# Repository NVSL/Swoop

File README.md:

# Swoop -- Read and Write Autodesk Eagle Files in Python

Swoop is a library of Python objects for representing and manipulating
Autodesk Eagle board, schematic, and library files used in designing printed
circuit boards (PCBs).  It parses an input Eagle file, creates a internal
representation data structure that represents the file's contents,
provides accessors and mutators to query, read, and modify those contents, and
generates valid Eagle files as output.

Documentation is available here: http://nvsl.ucsd.edu/Swoop

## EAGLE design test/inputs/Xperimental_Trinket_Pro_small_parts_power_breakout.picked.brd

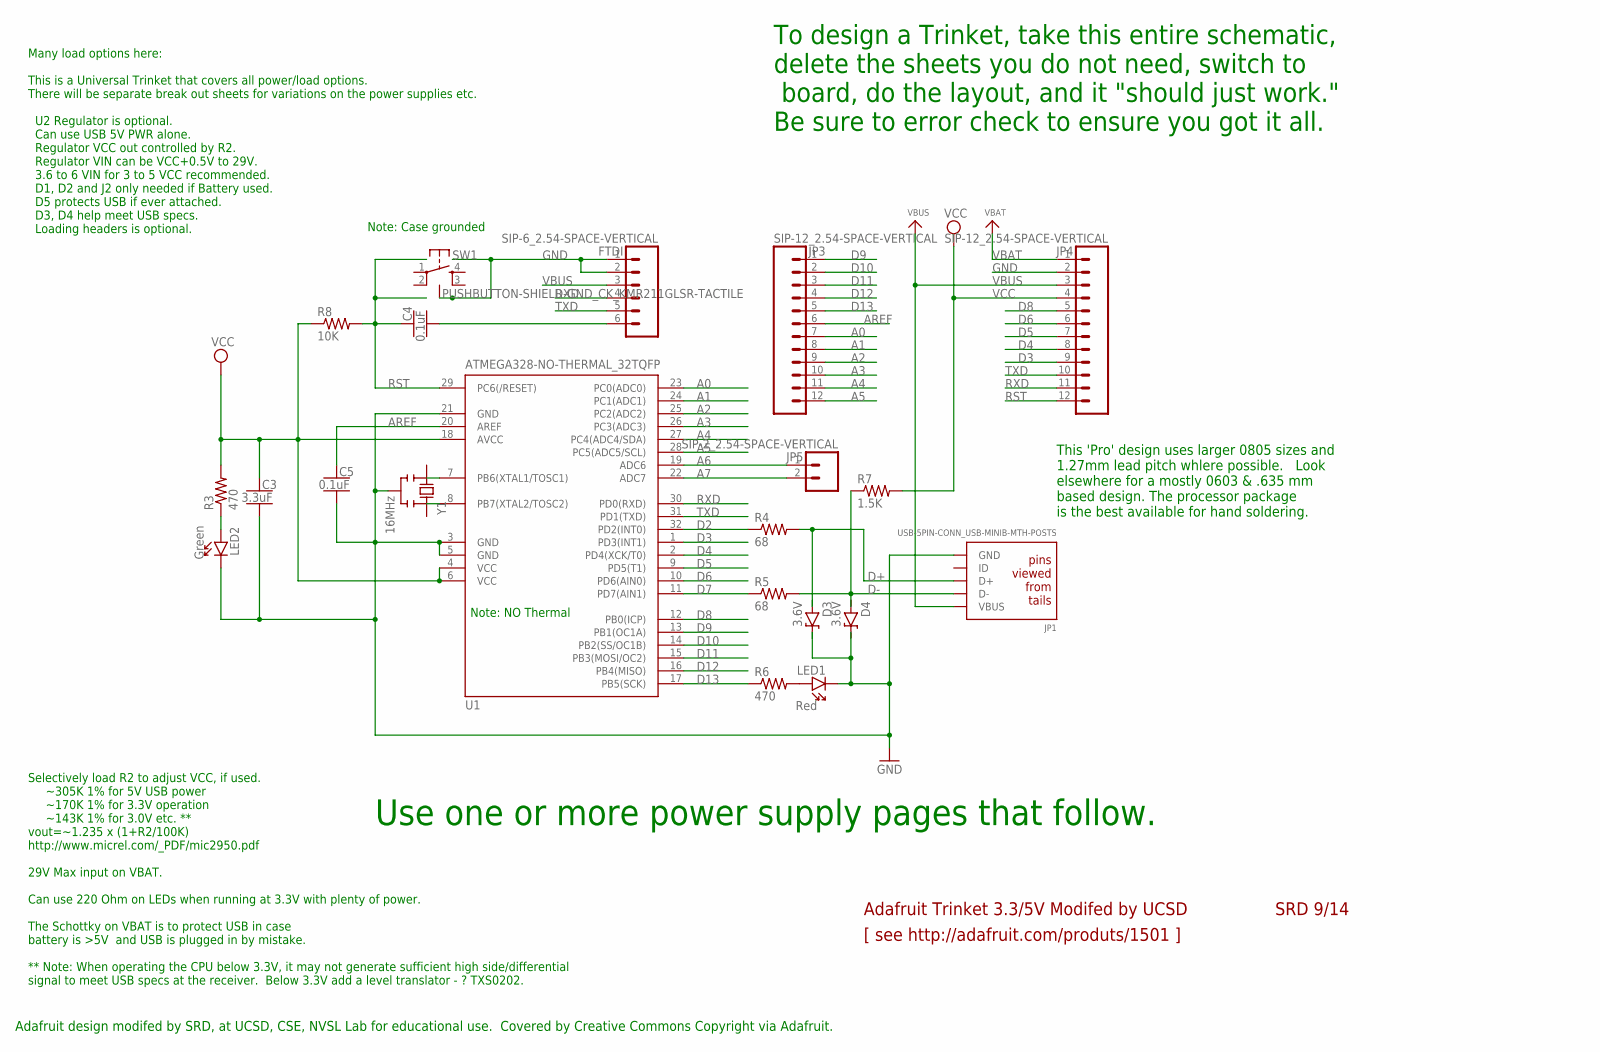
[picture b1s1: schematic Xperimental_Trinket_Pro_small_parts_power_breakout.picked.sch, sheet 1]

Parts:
C3: 3.3uF; CAPC2012X140_HS
C4, C5: 0.1uF; CAPRB500W53L600T350H600_HS
D3, D4: 3.6V; DIOAD1660W102L890D370_HS
FTDI: SIP-6_2.54-SPACE-VERTICAL; HDRV6W63P254_6X1_1524X254H838; MPN TSW-150-07-T-S
JP1: USB-5PIN-CONN_USB-MINIB-MTH-POSTS; FCI_10033526; MPN 10033526-N3212MLF
JP3, JP4: SIP-12_2.54-SPACE-VERTICAL; HDRV12W63P254_12X1_3048X254H838; MPN TSW-150-07-T-S
JP5: SIP-2_2.54-SPACE-VERTICAL; HDRV2W63P254_2X1_508X254H838; MPN TSW-150-07-T-S
LED1: Red; LEDRD250W50D400H640_HS
LED2: Green; LEDRD250W50D400H640_HS
R3, R6: 470; RESAD770W45L370D210_HS
R4, R5: 68; RESAD770W45L370D210_HS
R7: 1.5K; RESAD770W45L370D210_HS
R8: 10K; RESAD770W45L370D210_HS
SW1: PUSHBUTTON-SHIELD-GND_CK_KMR211GLSR-TACTILE; CK_KMR211GLSR; MPN KMR211GLFS
U1: ATMEGA328-NO-THERMAL_32TQFP; QFP80P900X900X120-32L30HS; MPN ATMEGA328-AU
Y1: 16MHz; MURATA_CTLS8_X_SERIES_HS

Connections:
A0: JP3.7, U1.23 (PC0(ADC0))
A1: JP3.8, U1.24 (PC1(ADC1))
A2: JP3.9, U1.25 (PC2(ADC2))
A3: JP3.10, U1.26 (PC3(ADC3))
A4: JP3.11, U1.27 (PC4(ADC4/SDA))
A5: JP3.12, U1.28 (PC5(ADC5/SCL))
A6: JP5.1, U1.19 (ADC6)
A7: JP5.2, U1.22 (ADC7)
AREF: C5.1, JP3.6, U1.20 (AREF)
D2: R4.1, U1.32 (PD2(INT0))
D3: JP4.9, U1.1 (PD3(INT1))
D4: JP4.8, U1.2 (PD4(XCK/T0))
D5: JP4.7, U1.9 (PD5(T1))
D6: JP4.6, U1.10 (PD6(AIN0))
D7: R5.1, U1.11 (PD7(AIN1))
D8: JP4.5, U1.12 (PB0(ICP))
D9: JP3.1, U1.13 (PB1(OC1A))
D10: JP3.2, U1.14 (PB2(SS/OC1B))
D11: JP3.3, U1.15 (PB3(MOSI/OC2))
D12: JP3.4, U1.16 (PB4(MISO))
D13: JP3.5, R6.1, U1.17 (PB5(SCK))
D+: D3.A, JP1.3 (D+), R4.2
D-: D4.A, JP1.2 (D-), R5.2, R7.1
DTR/RTS: C4.2, FTDI.6
GND: C3.2, C5.2, D3.C, D4.C, FTDI.1, FTDI.2, JP1.5 (GND), JP4.2, LED1.C, LED2.C, SW1.1, SW1.4, SW1.5, U1.3 (GND), U1.5 (GND), U1.21 (GND), Y1.2 (GND); also elsewhere on the board
unnamed: LED1.A, R6.2
unnamed: U1.8 (PB7(XTAL2/TOSC2)), Y1.1 (OSC2)
unnamed: U1.7 (PB6(XTAL1/TOSC1)), Y1.3 (OSC1)
unnamed: LED2.A, R3.1
RST: C4.1, JP4.12, R8.2, SW1.2, SW1.3, U1.29 (PC6(/RESET))
RXD: FTDI.4, JP4.11, U1.30 (PD0(RXD))
TXD: FTDI.5, JP4.10, U1.31 (PD1(TXD))
VBAT: JP4.1; also elsewhere on the board
VBUS: FTDI.3, JP1.1 (VBUS), JP4.3; also elsewhere on the board
VCC: C3.1, JP4.4, R3.2, R7.2, R8.1, U1.4 (VCC), U1.6 (VCC), U1.18 (AVCC); also elsewhere on the board

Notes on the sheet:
To design a Trinket, take this entire schematic, delete the sheets you do not need, switch to board, do the layout, and it "should just work." Be sure to error check to ensure you got it all.
[ see http://adafruit.com/produts/1501 ]
Adafruit Trinket 3.3/5V Modifed by UCSD
This 'Pro' design uses larger 0805 sizes and 1.27mm lead pitch whlere possible. Look elsewhere for a mostly 0603 & .635 mm based design. The processor package is the best available for hand soldering.
SRD 9/14
Adafruit design modifed by SRD, at UCSD, CSE, NVSL Lab for educational use. Covered by Creative Commons Copyright via Adafruit.
Many load options here: This is a Universal Trinket that covers all power/load options. There will be separate break out sheets for variations on the power supplies etc. U2 Regulator is optional. Can use USB 5V PWR alone. Regulator VCC out controlled by R2. Regulator VIN can be VCC+0.5V to 29V. 3.6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
Selectively load R2 to adjust VCC, if used. ~305K 1% for 5V USB power ~170K 1% for 3.3V operation ~143K 1% for 3.0V etc. ** vout=~1.235 x (1+R2/100K) http://www.micrel.com/_PDF/mic2950.pdf 29V Max input on VBAT. Can use 220 Ohm on LEDs when running at 3.3V with plenty of power. The Schottky on VBAT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
Note: Case grounded
Use one or more power supply pages that follow.
Note: NO Thermal

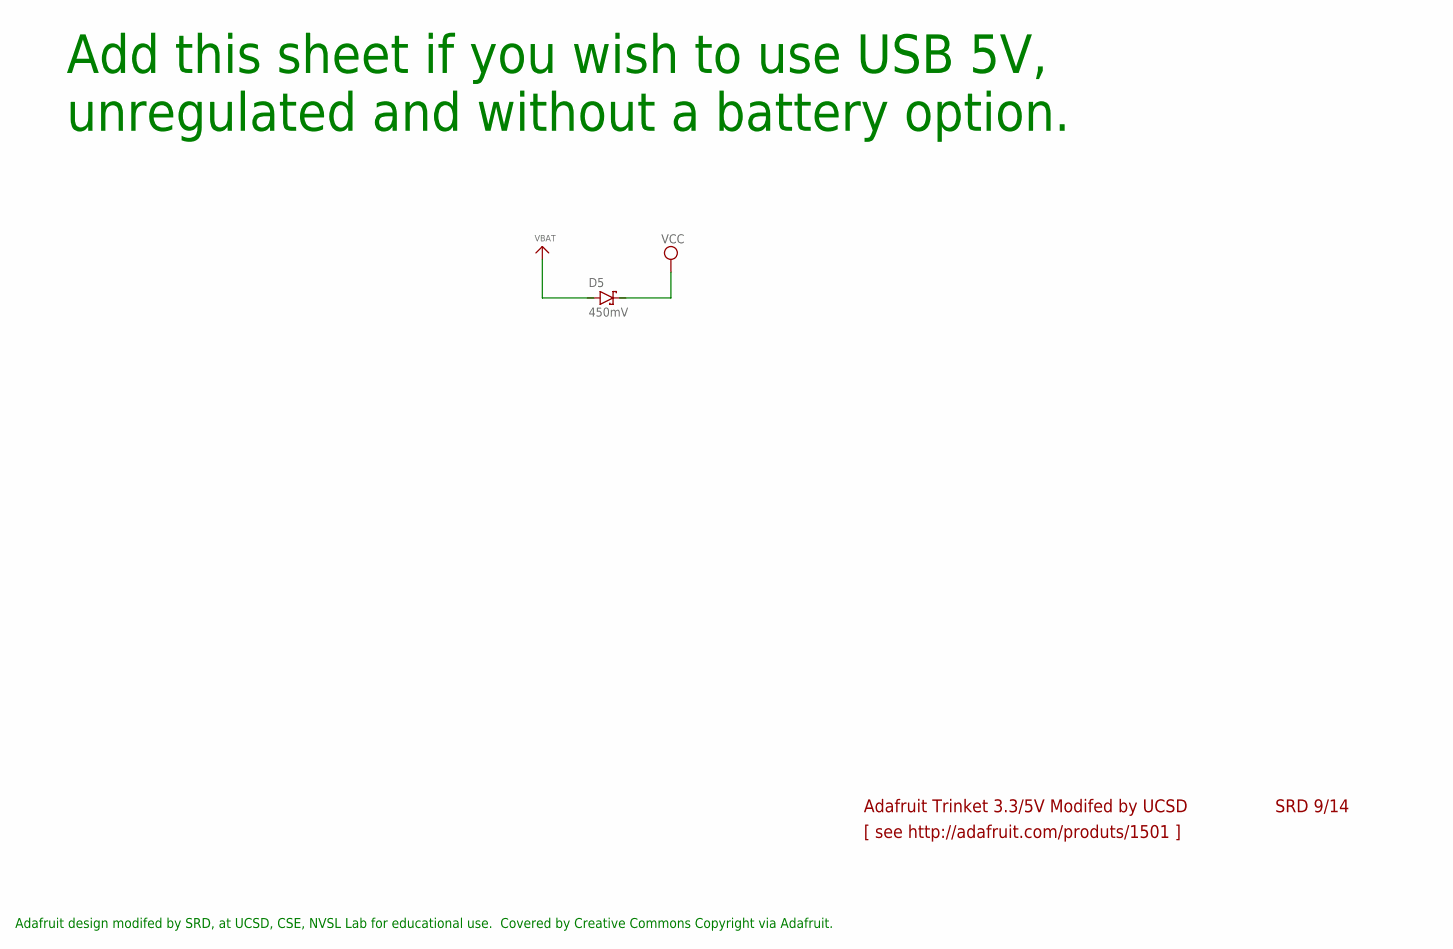
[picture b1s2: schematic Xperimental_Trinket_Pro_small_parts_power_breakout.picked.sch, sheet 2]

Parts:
D5: 450mV; DIOAD1125W78L520D270_HS

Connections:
VBAT: D5.A; also elsewhere on the board
VCC: D5.C; also elsewhere on the board

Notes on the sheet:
Add this sheet if you wish to use USB 5V, unregulated and without a battery option.
Adafruit design modifed by SRD, at UCSD, CSE, NVSL Lab for educational use. Covered by Creative Commons Copyright via Adafruit.
[ see http://adafruit.com/produts/1501 ]
Adafruit Trinket 3.3/5V Modifed by UCSD
SRD 9/14

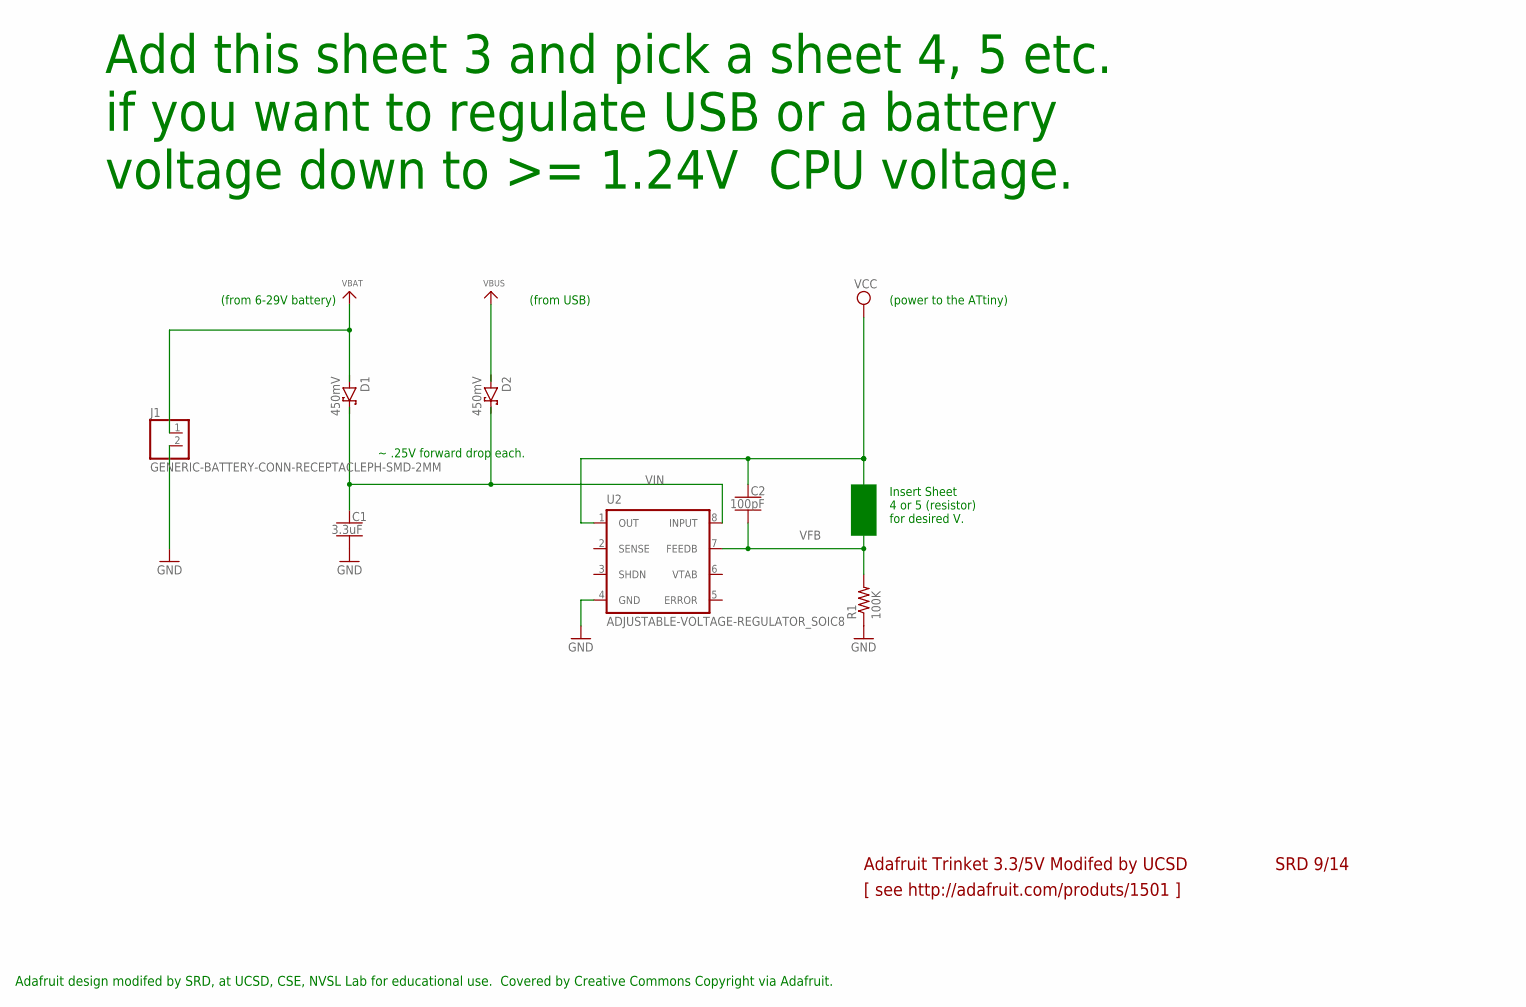
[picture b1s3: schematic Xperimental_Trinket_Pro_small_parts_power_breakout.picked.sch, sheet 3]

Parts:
C1: 3.3uF; CAPC2012X140_HS
C2: 100pF; CAPRB500W53L550T250H550_HS
D1, D2: 450mV; DIOAD1125W78L520D270_HS
J1: GENERIC-BATTERY-CONN-RECEPTACLEPH-SMD-2MM; JST_S2B-PH-SM4-TB; MPN S2B-PH-SM4-TB(LF)(SN)
R1: 100K; RESAD1160W55L680D260_HS
U2: ADJUSTABLE-VOLTAGE-REGULATOR_SOIC8; SOIC127P600X175-8L86HS; MPN MIC2951-03YM

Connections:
GND: C1.2, J1.2, R1.1, U2.4 (GND); also elsewhere on the board
VBAT: D1.A, J1.1; also elsewhere on the board
VBUS: D2.A; also elsewhere on the board
VCC: C2.1, U2.1 (OUT); also elsewhere on the board
VFB: C2.2, R1.2, U2.7 (FEEDB); also elsewhere on the board
VIN: C1.1, D1.C, D2.C, U2.8 (INPUT); also elsewhere on the board

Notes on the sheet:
(from USB)
[ see http://adafruit.com/produts/1501 ]
Adafruit Trinket 3.3/5V Modifed by UCSD
Insert Sheet 4 or 5 (resistor) for desired V.
(power to the ATtiny)
Add this sheet 3 and pick a sheet 4, 5 etc. if you want to regulate USB or a battery voltage down to >= 1.24V CPU voltage.
SRD 9/14
(from 6-29V battery)
Adafruit design modifed by SRD, at UCSD, CSE, NVSL Lab for educational use. Covered by Creative Commons Copyright via Adafruit.
~ .25V forward drop each.

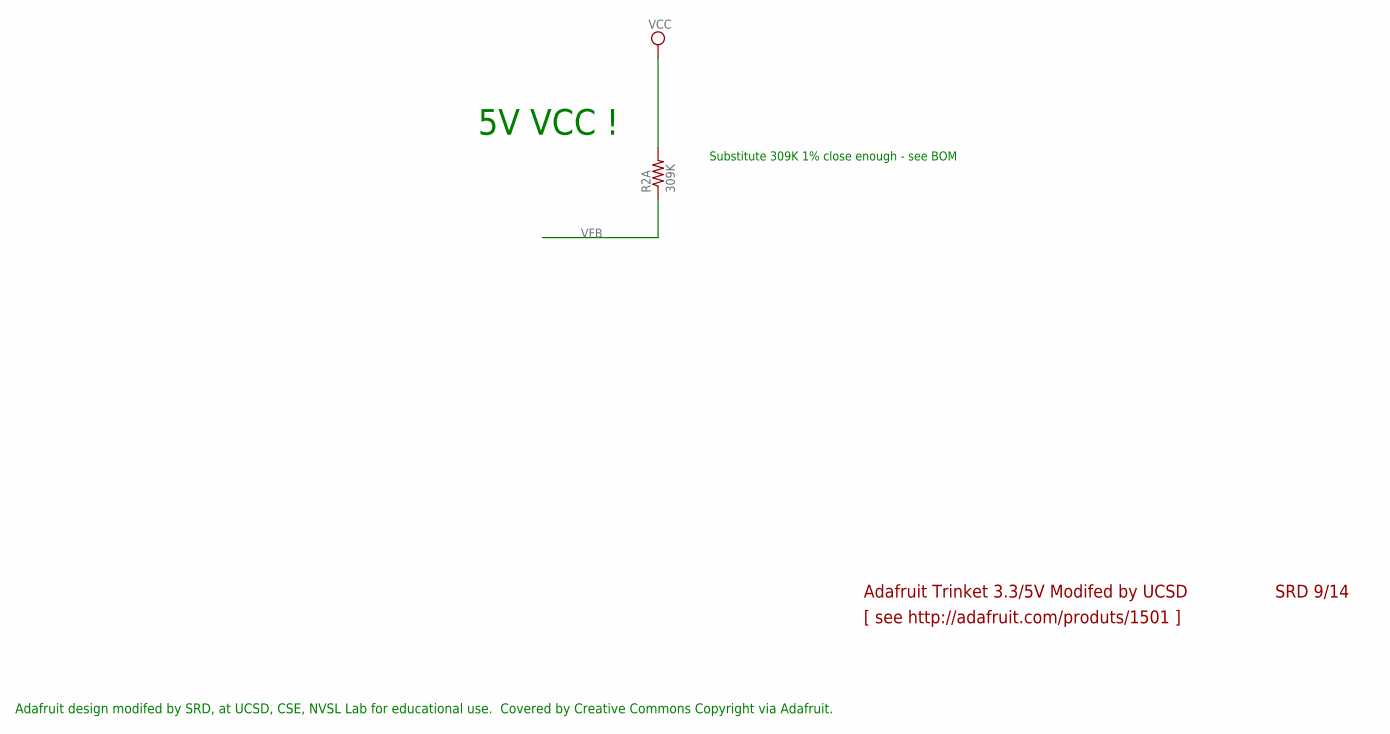
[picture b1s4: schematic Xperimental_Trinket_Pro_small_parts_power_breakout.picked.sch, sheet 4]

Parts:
R2A: 309K; RESAD1160W55L680D260_HS

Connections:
VCC: R2A.2; also elsewhere on the board
VFB: R2A.1; also elsewhere on the board

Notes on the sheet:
Substitute 309K 1% close enough - see BOM
[ see http://adafruit.com/produts/1501 ]
Adafruit Trinket 3.3/5V Modifed by UCSD
SRD 9/14
Adafruit design modifed by SRD, at UCSD, CSE, NVSL Lab for educational use. Covered by Creative Commons Copyright via Adafruit.
5V VCC !

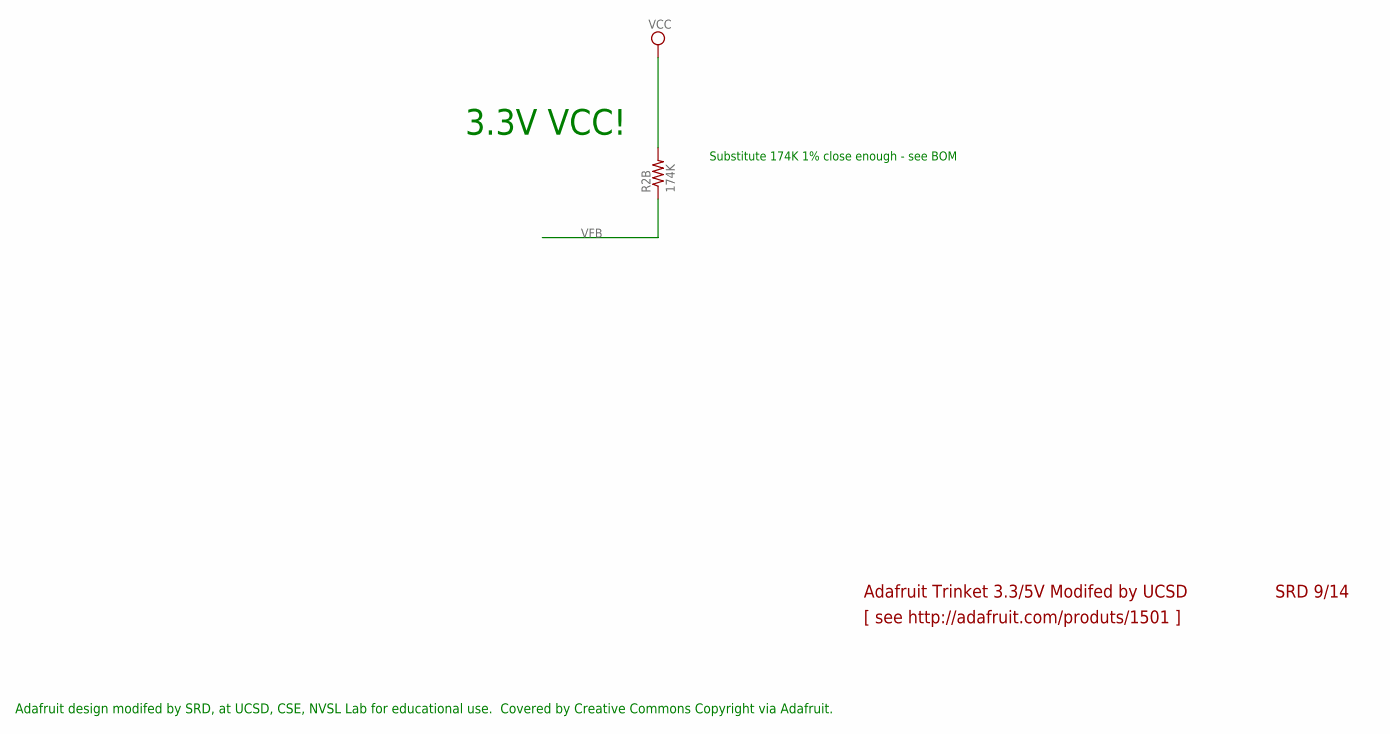
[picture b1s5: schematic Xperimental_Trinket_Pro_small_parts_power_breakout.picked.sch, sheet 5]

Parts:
R2B: 174K; RESAD1160W55L680D260_HS

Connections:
VCC: R2B.2; also elsewhere on the board
VFB: R2B.1; also elsewhere on the board

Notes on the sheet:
Substitute 174K 1% close enough - see BOM
[ see http://adafruit.com/produts/1501 ]
Adafruit Trinket 3.3/5V Modifed by UCSD
SRD 9/14
Adafruit design modifed by SRD, at UCSD, CSE, NVSL Lab for educational use. Covered by Creative Commons Copyright via Adafruit.
3.3V VCC!

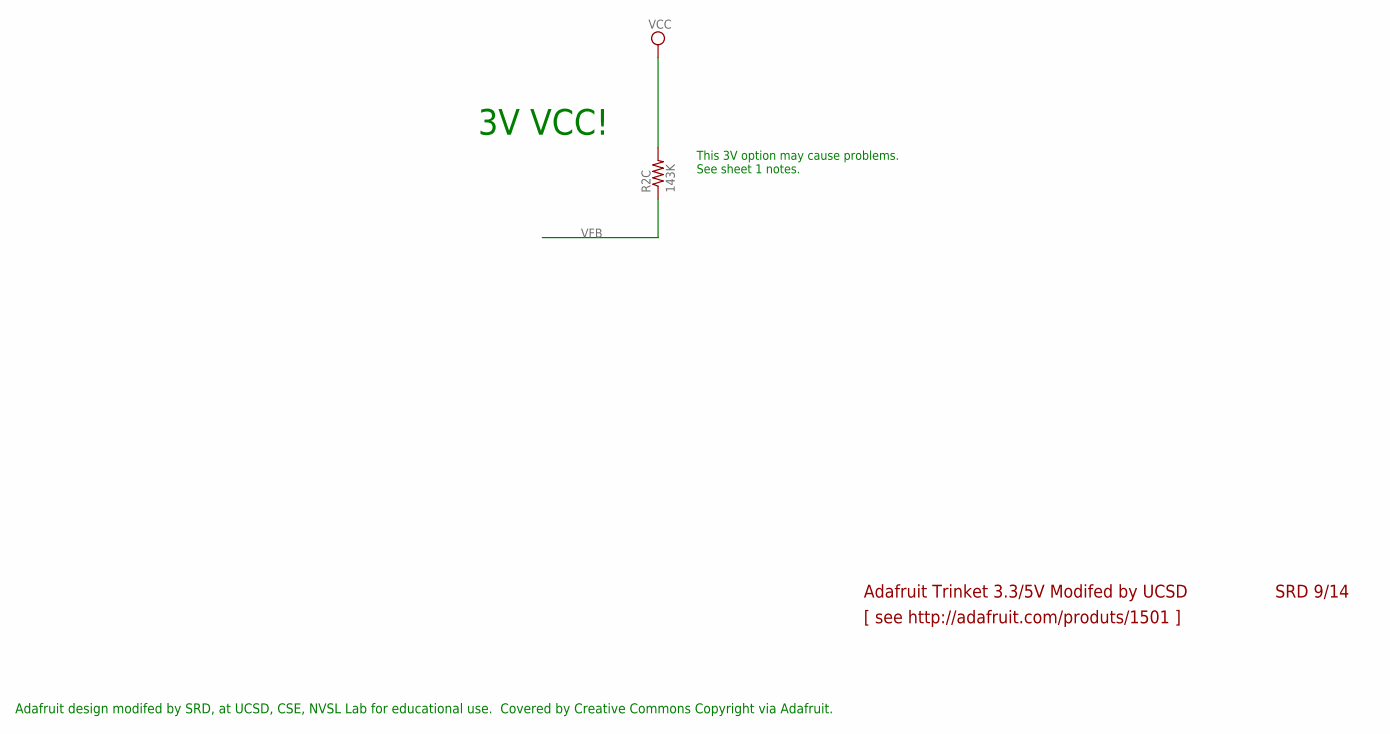
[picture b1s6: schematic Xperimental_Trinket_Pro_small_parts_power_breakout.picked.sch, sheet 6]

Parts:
R2C: 143K; RESAD1160W55L680D260_HS

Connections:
VCC: R2C.2; also elsewhere on the board
VFB: R2C.1; also elsewhere on the board

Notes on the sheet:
This 3V option may cause problems. See sheet 1 notes.
[ see http://adafruit.com/produts/1501 ]
Adafruit Trinket 3.3/5V Modifed by UCSD
SRD 9/14
Adafruit design modifed by SRD, at UCSD, CSE, NVSL Lab for educational use. Covered by Creative Commons Copyright via Adafruit.
3V VCC!

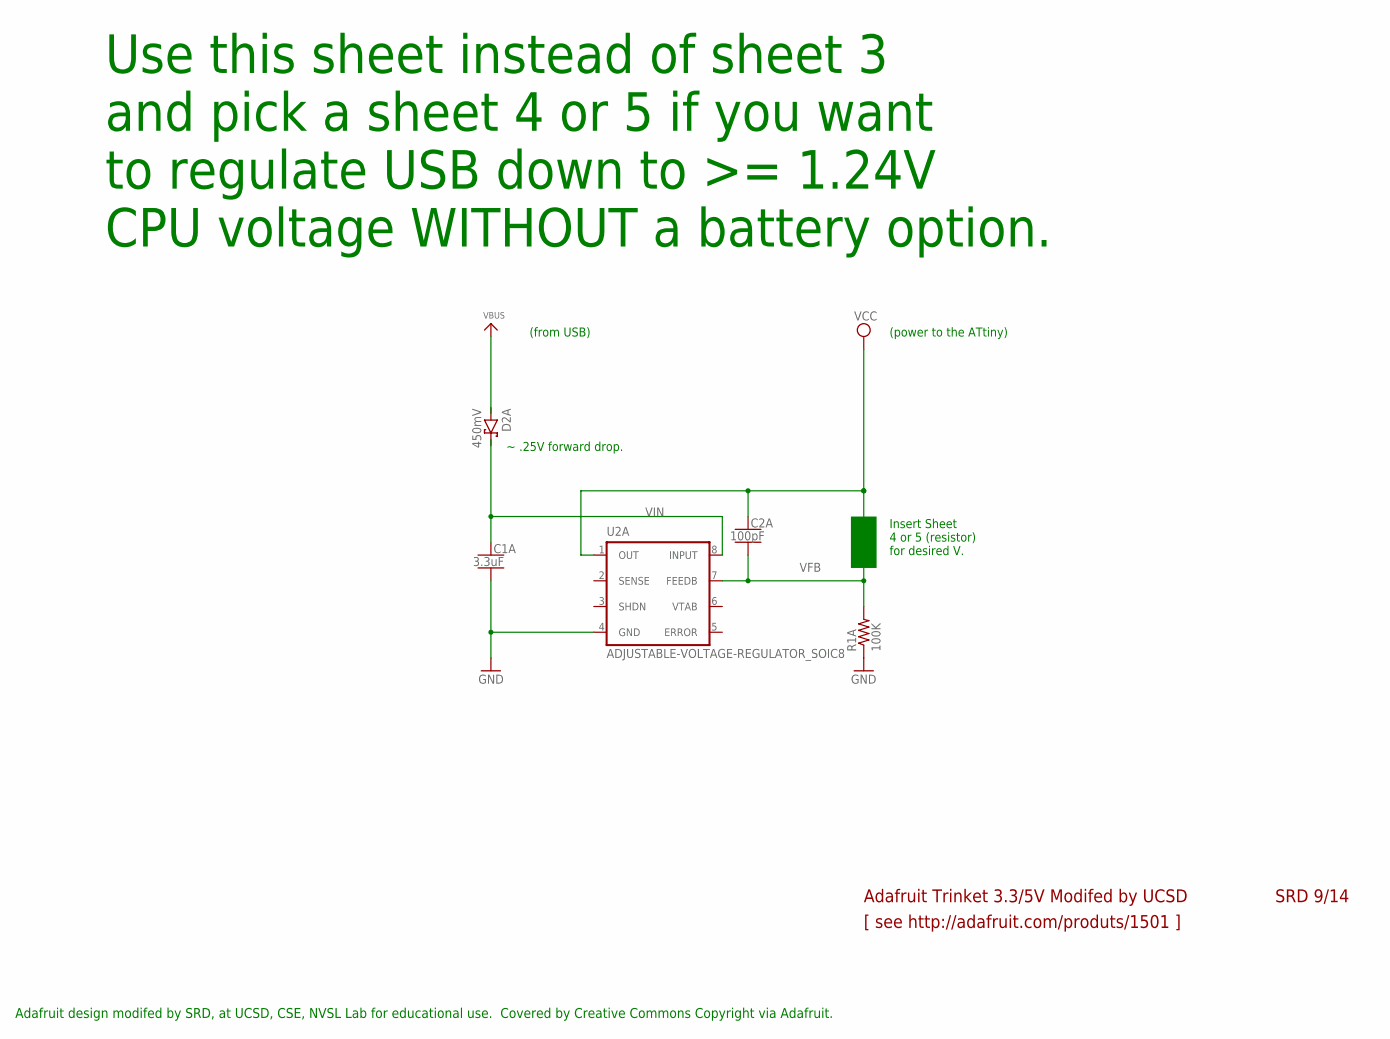
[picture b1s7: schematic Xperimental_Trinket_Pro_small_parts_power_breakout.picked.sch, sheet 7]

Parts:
C1A: 3.3uF; CAPC2012X140_HS
C2A: 100pF; CAPRB500W53L550T250H550_HS
D2A: 450mV; DIOAD1125W78L520D270_HS
R1A: 100K; RESAD1160W55L680D260_HS
U2A: ADJUSTABLE-VOLTAGE-REGULATOR_SOIC8; SOIC127P600X175-8L86HS; MPN MIC2951-03YM

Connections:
GND: C1A.2, R1A.1, U2A.4 (GND); also elsewhere on the board
VBUS: D2A.A; also elsewhere on the board
VCC: C2A.1, U2A.1 (OUT); also elsewhere on the board
VFB: C2A.2, R1A.2, U2A.7 (FEEDB); also elsewhere on the board
VIN: C1A.1, D2A.C, U2A.8 (INPUT); also elsewhere on the board

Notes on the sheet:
Adafruit design modifed by SRD, at UCSD, CSE, NVSL Lab for educational use. Covered by Creative Commons Copyright via Adafruit.
Use this sheet instead of sheet 3 and pick a sheet 4 or 5 if you want to regulate USB down to >= 1.24V CPU voltage WITHOUT a battery option.
Adafruit Trinket 3.3/5V Modifed by UCSD
[ see http://adafruit.com/produts/1501 ]
Insert Sheet 4 or 5 (resistor) for desired V.
(power to the ATtiny)
SRD 9/14
~ .25V forward drop.
(from USB)

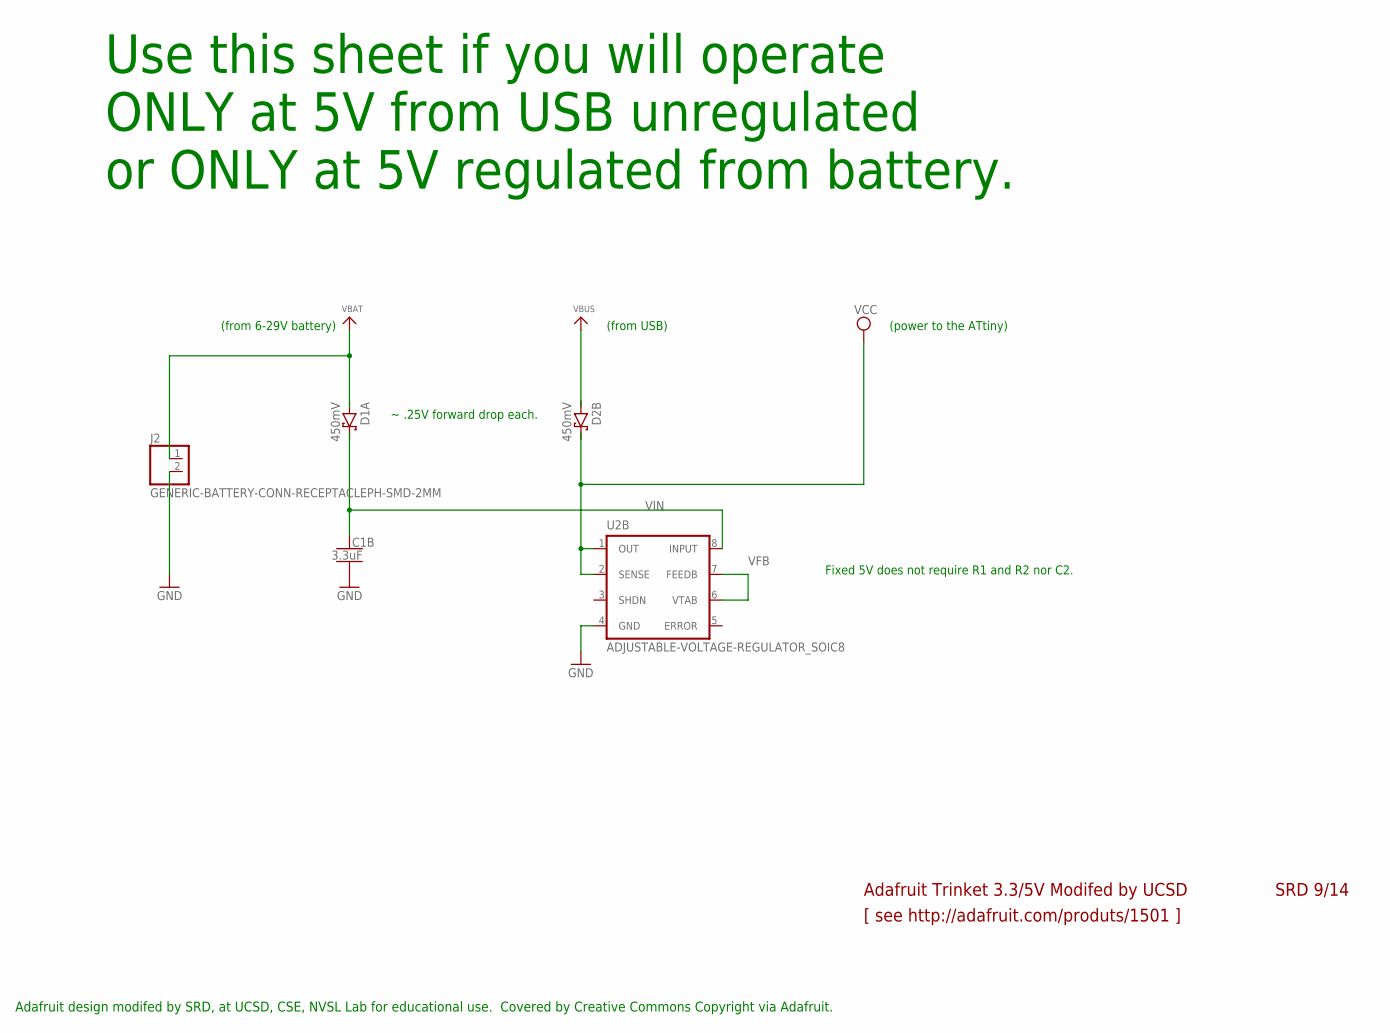
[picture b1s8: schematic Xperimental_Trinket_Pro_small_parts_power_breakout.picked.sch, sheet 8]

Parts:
C1B: 3.3uF; CAPC2012X140_HS
D1A, D2B: 450mV; DIOAD1125W78L520D270_HS
J2: GENERIC-BATTERY-CONN-RECEPTACLEPH-SMD-2MM; JST_S2B-PH-SM4-TB; MPN S2B-PH-SM4-TB(LF)(SN)
U2B: ADJUSTABLE-VOLTAGE-REGULATOR_SOIC8; SOIC127P600X175-8L86HS; MPN MIC2951-03YM

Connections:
GND: C1B.2, J2.2, U2B.4 (GND); also elsewhere on the board
VBAT: D1A.A, J2.1; also elsewhere on the board
VBUS: D2B.A; also elsewhere on the board
VCC: D2B.C, U2B.1 (OUT), U2B.2 (SENSE); also elsewhere on the board
VFB: U2B.6 (VTAB), U2B.7 (FEEDB); also elsewhere on the board
VIN: C1B.1, D1A.C, U2B.8 (INPUT); also elsewhere on the board

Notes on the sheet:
(from 6-29V battery)
Use this sheet if you will operate ONLY at 5V from USB unregulated or ONLY at 5V regulated from battery.
Adafruit design modifed by SRD, at UCSD, CSE, NVSL Lab for educational use. Covered by Creative Commons Copyright via Adafruit.
Fixed 5V does not require R1 and R2 nor C2.
Adafruit Trinket 3.3/5V Modifed by UCSD
[ see http://adafruit.com/produts/1501 ]
(power to the ATtiny)
SRD 9/14
~ .25V forward drop each.
(from USB)

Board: 2 copper layers, 42 parts (0 on the bottom side), 37 nets, no tracks yet.

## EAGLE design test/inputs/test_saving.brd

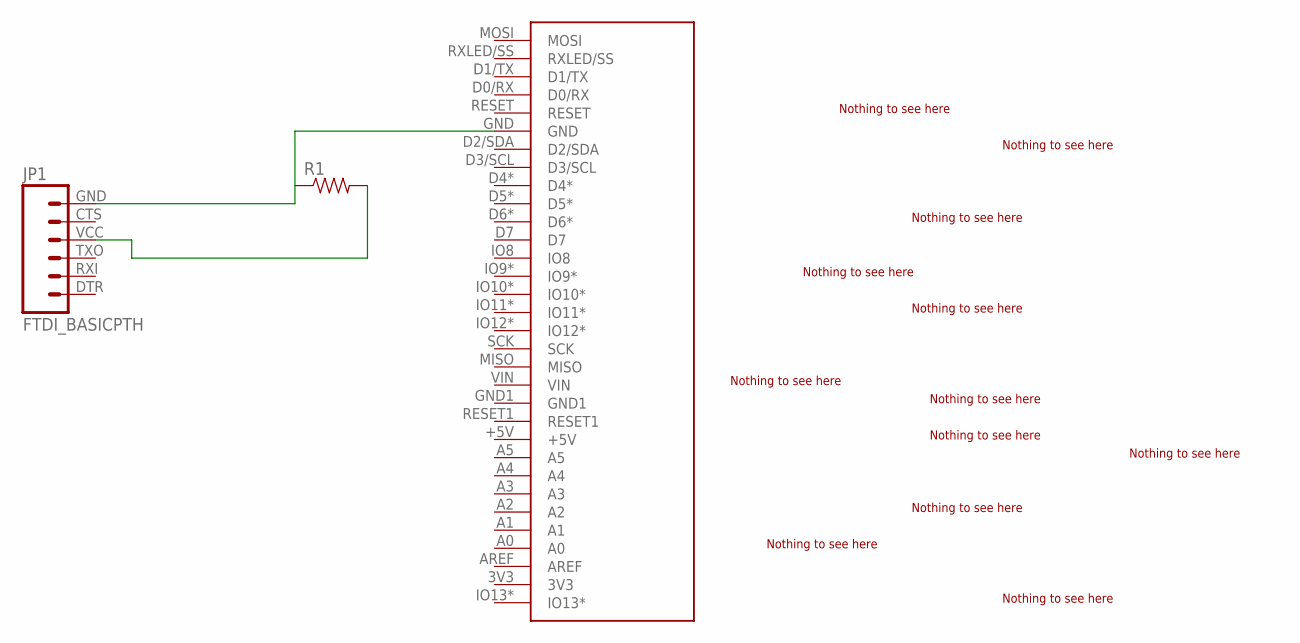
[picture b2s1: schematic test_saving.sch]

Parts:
ARDUINO: ARDUINO_MICRO_REV03J-BOB; ARDUINO_MICRO_REV03J
JP1: FTDI_BASICPTH; FTDI_BASIC
R1: RESISTOR0805-RES; 0805
TEST-ARC1: TEST-ARC
TEST-ARC3: TEST-ARC3
TEST-CIRCLE: TEST-CIRCLE
TEST-HOLE: TEST-HOLE
TEST-PAD1: TEST-PAD1
TEST-PAD2: TEST-PAD2
TEST-PAD-OCT: TEST-PAD-OCT
TEST-PAD-OCT2: TEST-PAD-OCT2
TEST-PAD-ROT: TEST-PAD-ROT
TEST-PAD-ROUND: TEST-PAD-ROUND
TEST-PAD-SQUARE: TEST-PAD3
TEST-PAD-SQUARE-ROT: TEST-PAD-SQUARE-ROT

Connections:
unnamed: ARDUINO.GND, JP1.GND (6), R1.1
unnamed: JP1.VCC (4), R1.2

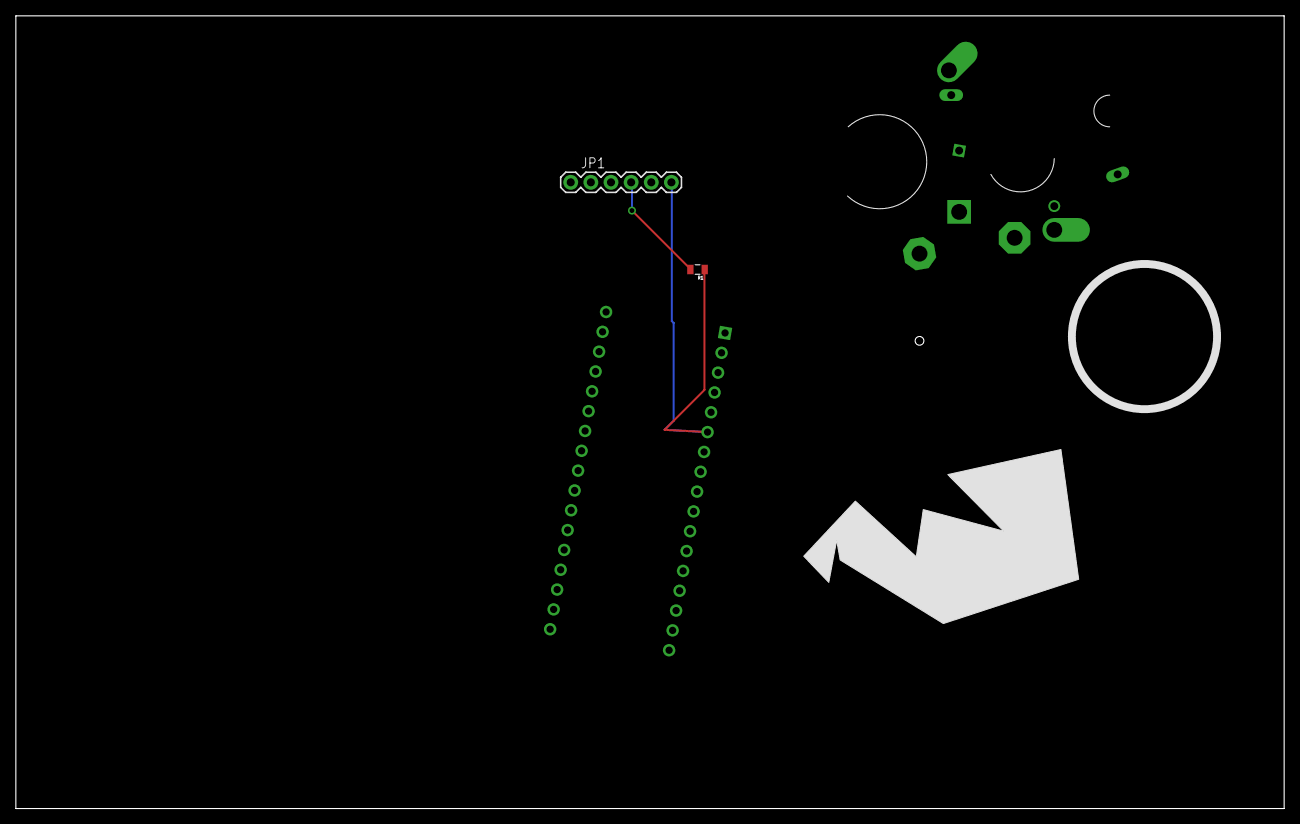
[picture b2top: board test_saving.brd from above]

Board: 2 copper layers, 160.0 x 100.0 mm, 18 parts (1 on the bottom side), 2 nets.

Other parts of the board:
TEST-ARC2: TEST-ARC2
TEST-PAD3: TEST-PAD1
TEST-POLYGON: TEST-POLYGON

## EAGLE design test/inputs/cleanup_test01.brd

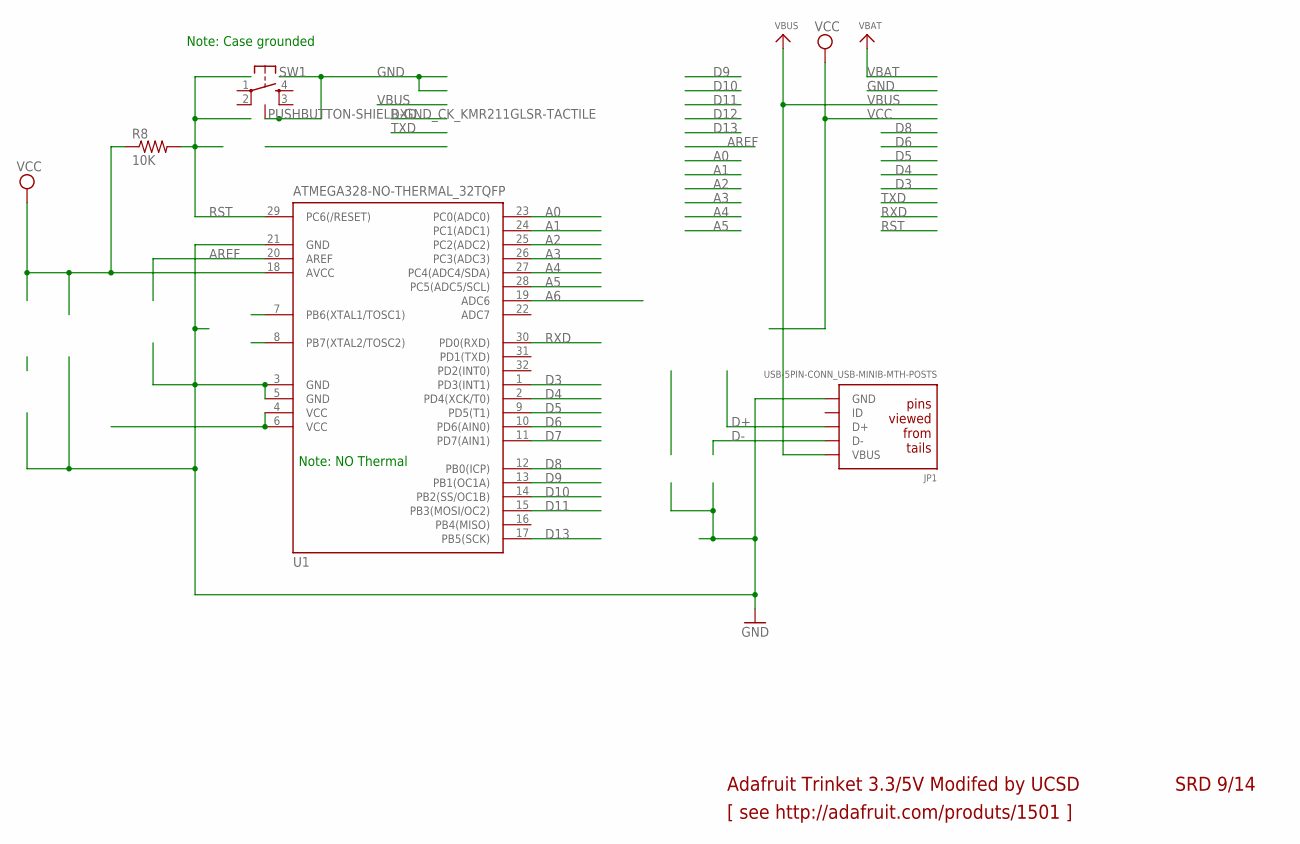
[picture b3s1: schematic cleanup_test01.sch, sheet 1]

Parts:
JP1: USB-5PIN-CONN_USB-MINIB-MTH-POSTS; FCI_10033526; MPN 10033526-N3212MLF
SW1: PUSHBUTTON-SHIELD-GND_CK_KMR211GLSR-TACTILE; CK_KMR211GLSR; MPN KMR211GLFS
U1: ATMEGA328-NO-THERMAL_32TQFP; QFP80P900X900X120-32L30HS; MPN ATMEGA328-AU

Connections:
A0: U1.23 (PC0(ADC0))
A1: U1.24 (PC1(ADC1))
A2: U1.25 (PC2(ADC2))
A3: U1.26 (PC3(ADC3))
A4: U1.27 (PC4(ADC4/SDA))
A5: U1.28 (PC5(ADC5/SCL))
A6: U1.19 (ADC6)
AREF: U1.20 (AREF)
D3: U1.1 (PD3(INT1))
D4: U1.2 (PD4(XCK/T0))
D5: U1.9 (PD5(T1))
D6: U1.10 (PD6(AIN0))
D7: U1.11 (PD7(AIN1))
D8: U1.12 (PB0(ICP))
D9: U1.13 (PB1(OC1A))
D10: U1.14 (PB2(SS/OC1B))
D11: U1.15 (PB3(MOSI/OC2))
D13: U1.17 (PB5(SCK))
D+: JP1.3 (D+)
D-: JP1.2 (D-)
GND: JP1.5 (GND), SW1.1, SW1.4, SW1.5, U1.3 (GND), U1.5 (GND), U1.21 (GND)
unnamed: U1.4 (VCC), U1.6 (VCC)
RST: SW1.2, SW1.3, U1.29 (PC6(/RESET))
RXD: U1.30 (PD0(RXD))
VBUS: JP1.1 (VBUS)
VCC: U1.18 (AVCC)

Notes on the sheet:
[ see http://adafruit.com/produts/1501 ]
Adafruit Trinket 3.3/5V Modifed by UCSD
SRD 9/14
Note: Case grounded
Note: NO Thermal

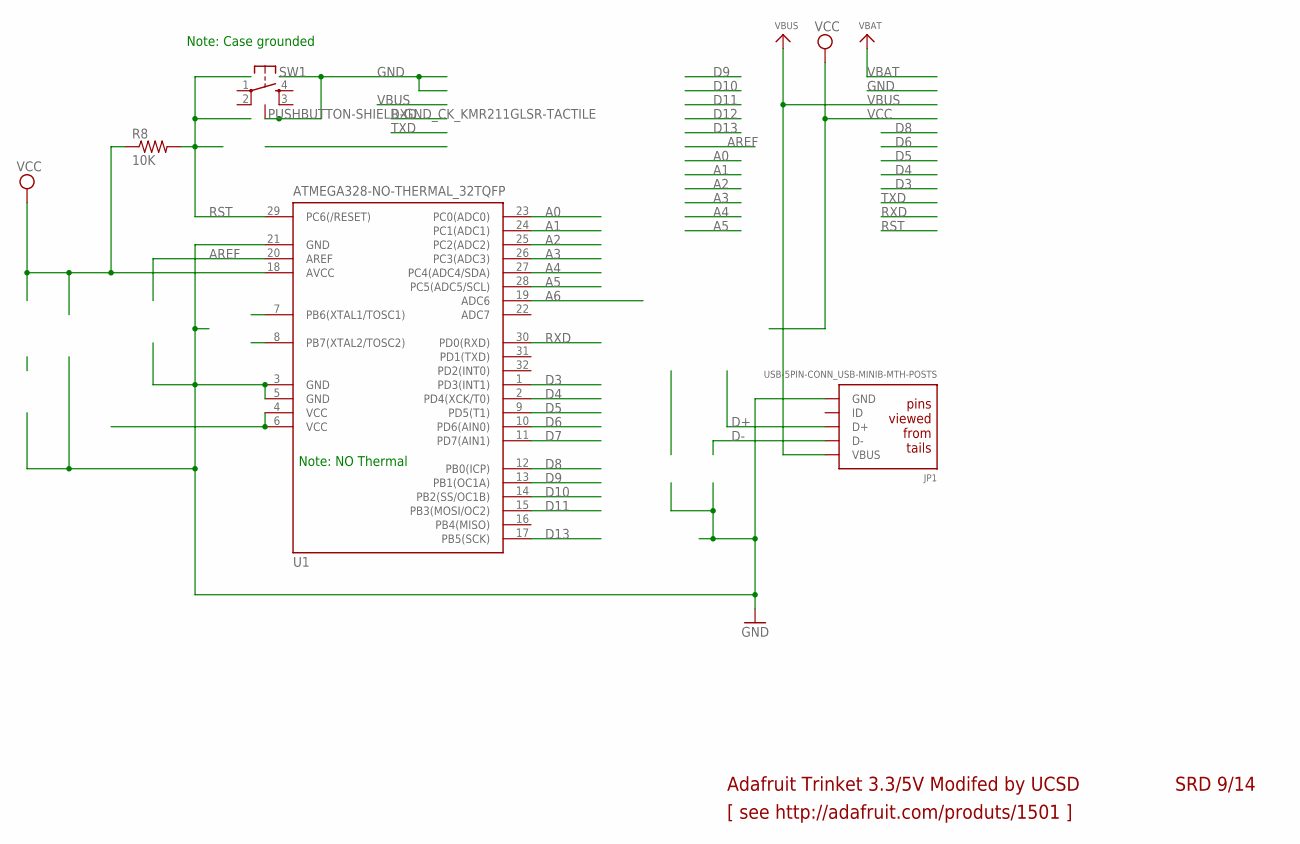
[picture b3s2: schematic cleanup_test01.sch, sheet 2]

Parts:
JP1: USB-5PIN-CONN_USB-MINIB-MTH-POSTS; FCI_10033526; MPN 10033526-N3212MLF
SW1: PUSHBUTTON-SHIELD-GND_CK_KMR211GLSR-TACTILE; CK_KMR211GLSR; MPN KMR211GLFS
U1: ATMEGA328-NO-THERMAL_32TQFP; QFP80P900X900X120-32L30HS; MPN ATMEGA328-AU

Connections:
A0: U1.23 (PC0(ADC0))
A1: U1.24 (PC1(ADC1))
A2: U1.25 (PC2(ADC2))
A3: U1.26 (PC3(ADC3))
A4: U1.27 (PC4(ADC4/SDA))
A5: U1.28 (PC5(ADC5/SCL))
A6: U1.19 (ADC6)
AREF: U1.20 (AREF)
D3: U1.1 (PD3(INT1))
D4: U1.2 (PD4(XCK/T0))
D5: U1.9 (PD5(T1))
D6: U1.10 (PD6(AIN0))
D7: U1.11 (PD7(AIN1))
D8: U1.12 (PB0(ICP))
D9: U1.13 (PB1(OC1A))
D10: U1.14 (PB2(SS/OC1B))
D11: U1.15 (PB3(MOSI/OC2))
D13: U1.17 (PB5(SCK))
D+: JP1.3 (D+)
D-: JP1.2 (D-)
GND: JP1.5 (GND), SW1.1, SW1.4, SW1.5, U1.3 (GND), U1.5 (GND), U1.21 (GND)
unnamed: U1.4 (VCC), U1.6 (VCC)
RST: SW1.2, SW1.3, U1.29 (PC6(/RESET))
RXD: U1.30 (PD0(RXD))
VBUS: JP1.1 (VBUS)
VCC: U1.18 (AVCC)

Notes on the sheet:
[ see http://adafruit.com/produts/1501 ]
Adafruit Trinket 3.3/5V Modifed by UCSD
SRD 9/14
Note: Case grounded
Note: NO Thermal

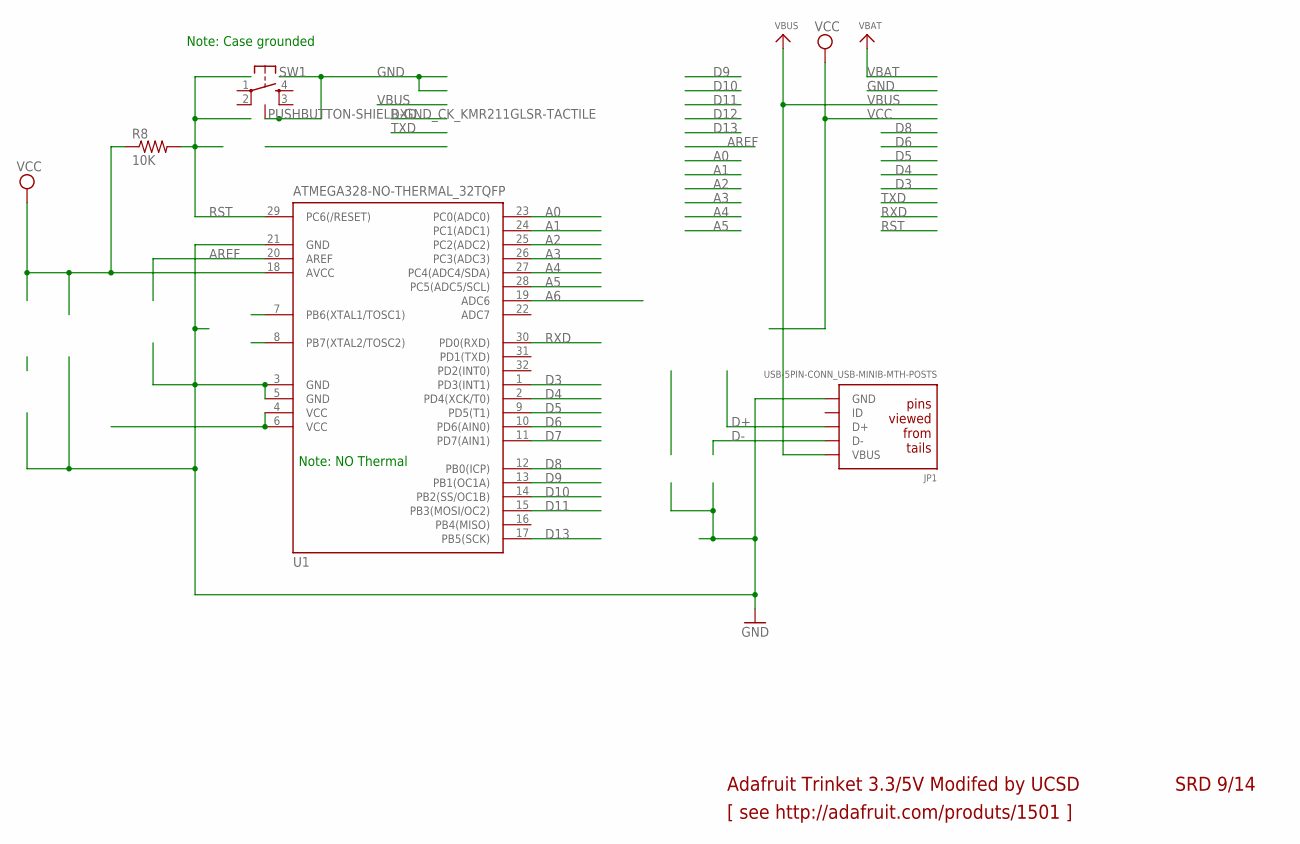
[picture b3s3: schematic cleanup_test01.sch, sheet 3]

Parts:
JP1: USB-5PIN-CONN_USB-MINIB-MTH-POSTS; FCI_10033526; MPN 10033526-N3212MLF
SW1: PUSHBUTTON-SHIELD-GND_CK_KMR211GLSR-TACTILE; CK_KMR211GLSR; MPN KMR211GLFS
U1: ATMEGA328-NO-THERMAL_32TQFP; QFP80P900X900X120-32L30HS; MPN ATMEGA328-AU

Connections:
A0: U1.23 (PC0(ADC0))
A1: U1.24 (PC1(ADC1))
A2: U1.25 (PC2(ADC2))
A3: U1.26 (PC3(ADC3))
A4: U1.27 (PC4(ADC4/SDA))
A5: U1.28 (PC5(ADC5/SCL))
A6: U1.19 (ADC6)
AREF: U1.20 (AREF)
D3: U1.1 (PD3(INT1))
D4: U1.2 (PD4(XCK/T0))
D5: U1.9 (PD5(T1))
D6: U1.10 (PD6(AIN0))
D7: U1.11 (PD7(AIN1))
D8: U1.12 (PB0(ICP))
D9: U1.13 (PB1(OC1A))
D10: U1.14 (PB2(SS/OC1B))
D11: U1.15 (PB3(MOSI/OC2))
D13: U1.17 (PB5(SCK))
D+: JP1.3 (D+)
D-: JP1.2 (D-)
GND: JP1.5 (GND), SW1.1, SW1.4, SW1.5, U1.3 (GND), U1.5 (GND), U1.21 (GND)
unnamed: U1.4 (VCC), U1.6 (VCC)
RST: SW1.2, SW1.3, U1.29 (PC6(/RESET))
RXD: U1.30 (PD0(RXD))
VBUS: JP1.1 (VBUS)
VCC: U1.18 (AVCC)

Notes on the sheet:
[ see http://adafruit.com/produts/1501 ]
Adafruit Trinket 3.3/5V Modifed by UCSD
SRD 9/14
Note: Case grounded
Note: NO Thermal

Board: 2 copper layers, 3 parts (0 on the bottom side), 3 nets, no tracks yet.

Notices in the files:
parts and their libraries:
microbuilder: This work is placed in the public domain, and may be freely used for commercial and non-commercial work with the following conditions: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
SparkFun-Connectors: Licensing: Creative Commons ShareAlike 4.0 International - https://creativecommons.org/licenses/by-sa/4.0
